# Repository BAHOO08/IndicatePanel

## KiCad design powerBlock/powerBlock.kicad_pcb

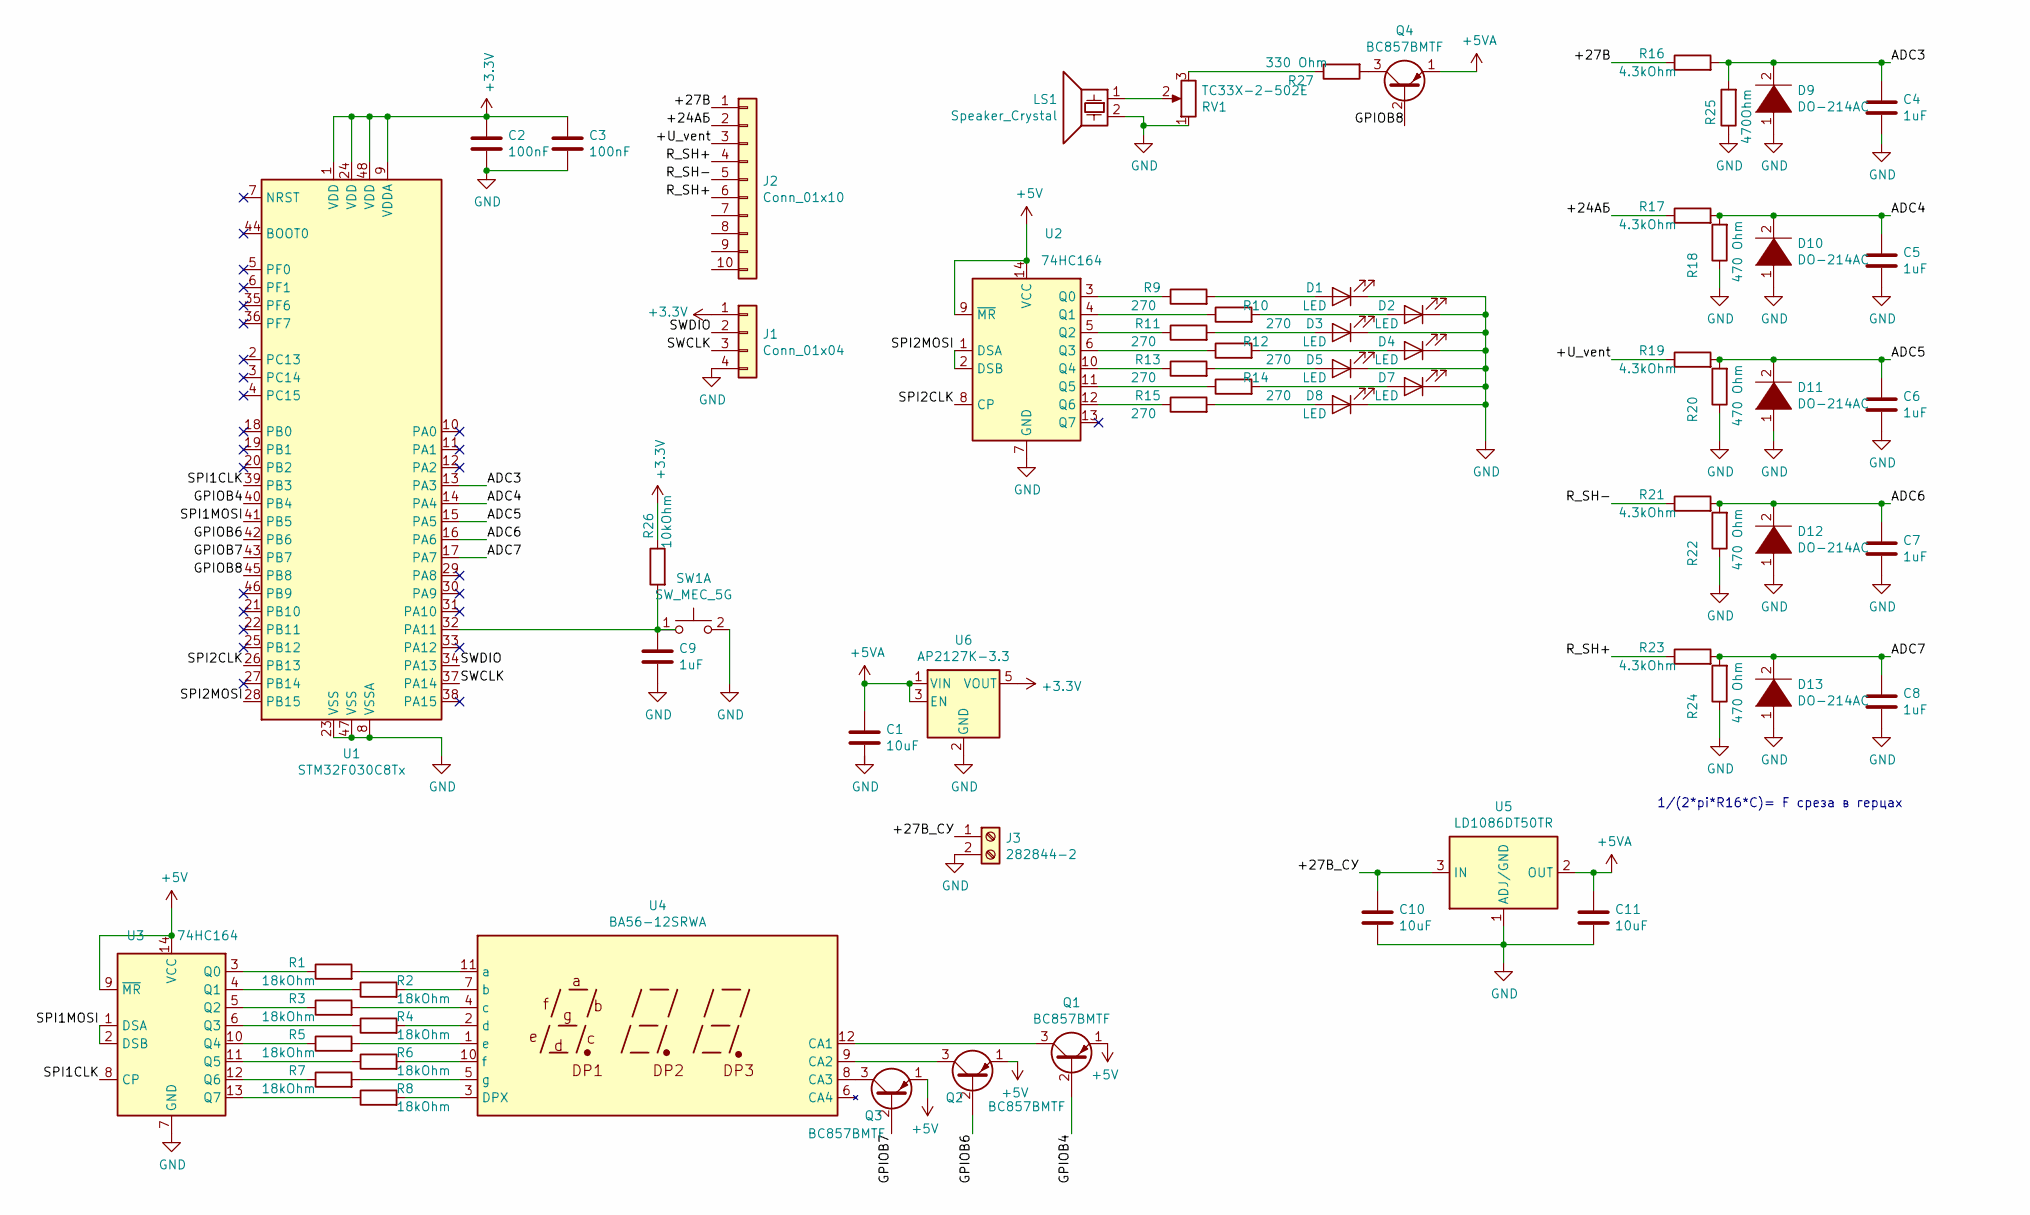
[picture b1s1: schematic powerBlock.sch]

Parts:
C1, C10, C11: 10uF; C_0603_1608Metric
C2, C3: 100nF; C_0603_1608Metric
C4, C5, C6, C7, C8, C9: 1uF; C_0603_1608Metric
D1, D2, D3, D4, D5, D7, D8: LED; LED_Rectangular_W3.9mm_H1.8mm
D9, D10, D11, D12, D13: DO-214AC; D_SMA
J1: Conn_01x04; PinHeader_1x04_P2.54mm_Vertical
J2: Conn_01x10; PinHeader_1x10_P2.54mm_Horizontal
J3: 282844-2; TerminalBlock_MetzConnect_Type175_RT02702HBLC_1x02_P7.50mm_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
LS1: Speaker_Crystal; R_LDR_10x8.5mm_P7.6mm_Vertical
Q1, Q2, Q3, Q4: BC857BMTF; SOT-23
R1, R2, R3, R4, R5, R6, R7, R8: 18kOhm; R_0603_1608Metric
R9, R10, R11, R12, R13, R14, R15: 270; R_0603_1608Metric
R16, R17, R19, R21, R23: 4.3kOhm; R_0603_1608Metric
R18, R20, R22, R24: 470 Ohm; R_0603_1608Metric
R25: 470Ohm; R_0603_1608Metric
R26: 10kOhm; R_0603_1608Metric
R27: 330 Ohm; R_0603_1608Metric
RV1: TC33X-2-502E; Potentiometer_Bourns_TC33X_Vertical
SW1: SW_MEC_5G; SW_SPST_PTS645
U1: STM32F030C8Tx; LQFP-48_7x7mm_P0.5mm
U2, U3: 74HC164; SOIC-14_3.9x8.7mm_P1.27mm
U4: BA56-12SRWA; CA56-12SEKWA
U5: LD1086DT50TR; TO-252-2
U6: AP2127K-3.3; SOT-23-5

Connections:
+3V3: C2.1, C3.1, J1.1, R26.1, U1.1 (VDD), U1.9 (VDDA), U1.24 (VDD), U1.48 (VDD), U6.5 (VOUT)
+5V: Q1.1 (E), Q2.1 (E), Q3.1 (E), U2.9 (~MR), U2.14 (VCC), U3.9 (~MR), U3.14 (VCC)
+5VA: C1.1, C11.1, Q4.1 (E), U5.2 (OUT), U6.1 (VIN), U6.3 (EN)
/+24АБ: J2.2, R17.1
/+27В: J2.1, R16.1
/+27В_СУ: C10.1, J3.1, U5.3 (IN)
/+U_vent: J2.3, R19.1
/ADC3: C4.1, D9.2 (A), R16.2, R25.2, U1.13 (PA3)
/ADC4: C5.1, D10.2 (A), R17.2, R18.2, U1.14 (PA4)
/ADC5: C6.1, D11.2 (A), R19.2, R20.2, U1.15 (PA5)
/ADC6: C7.1, D12.2 (A), R21.2, R22.2, U1.16 (PA6)
/ADC7: C8.1, D13.2 (A), R23.2, R24.2, U1.17 (PA7)
/GPIOB4: Q1.2 (B), U1.40 (PB4)
/GPIOB6: Q2.2 (B), U1.42 (PB6)
/GPIOB7: Q3.2 (B), U1.43 (PB7)
/GPIOB8: Q4.2 (B), U1.45 (PB8)
/R_SH+: J2.4, J2.6, R23.1
/R_SH-: J2.5, R21.1
/SPI1CLK: U1.39 (PB3), U3.8 (CP)
/SPI1MOSI: U1.41 (PB5), U3.1 (DSA), U3.2 (DSB)
/SPI2CLK: U1.26 (PB13), U2.8 (CP)
/SPI2MOSI: U1.28 (PB15), U2.1 (DSA), U2.2 (DSB)
/SWCLK: J1.3, U1.37 (PA14)
/SWDIO: J1.2, U1.34 (PA13)
GND: C2.2, C3.2, C4.2, C5.2, C6.2, C7.2, C8.2, C9.2, C10.2, C11.2, D1.1 (K), D2.1 (K), D3.1 (K), D4.1 (K), D5.1 (K), D7.1 (K), D8.1 (K), D9.1 (K), D10.1 (K), D11.1 (K), D12.1 (K), D13.1 (K), J1.4, J3.2, LS1.2, R18.1, R20.1, R22.1, R24.1, R25.1, RV1.1, SW1.2 (D), U1.8 (VSSA), U1.23 (VSS), U1.47 (VSS), U2.7 (GND), U3.7 (GND), U5.1 (ADJ/GND), U6.2 (GND)
unnamed: C9.1, R26.2, SW1.1 (C), U1.32 (PA11)
unnamed: D1.2 (A), R9.2
unnamed: D2.2 (A), R10.2
unnamed: D3.2 (A), R11.2
unnamed: D4.2 (A), R12.2
unnamed: D5.2 (A), R13.2
unnamed: D7.2 (A), R14.2
unnamed: D8.2 (A), R15.2
unnamed: LS1.1, RV1.2
unnamed: Q1.3 (C), U4.12 (CA1)
unnamed: Q2.3 (C), U4.9 (CA2)
unnamed: Q3.3 (C), U4.8 (CA3)
unnamed: Q4.3 (C), R27.2
unnamed: R1.1, U3.3 (Q0)
unnamed: R1.2, U4.11 (a)
unnamed: R2.1, U3.4 (Q1)
unnamed: R2.2, U4.7 (b)
unnamed: R3.1, U3.5 (Q2)
unnamed: R3.2, U4.4 (c)
unnamed: R4.1, U3.6 (Q3)
unnamed: R4.2, U4.2 (d)
unnamed: R5.1, U3.10 (Q4)
unnamed: R5.2, U4.1 (e)
unnamed: R6.1, U3.11 (Q5)
unnamed: R6.2, U4.10 (f)
unnamed: R7.1, U3.12 (Q6)
unnamed: R7.2, U4.5 (g)
unnamed: R8.1, U3.13 (Q7)
unnamed: R8.2, U4.3 (DPX)
unnamed: R9.1, U2.3 (Q0)
unnamed: R10.1, U2.4 (Q1)
unnamed: R11.1, U2.5 (Q2)
unnamed: R12.1, U2.6 (Q3)
unnamed: R13.1, U2.10 (Q4)
unnamed: R14.1, U2.11 (Q5)
unnamed: R15.1, U2.12 (Q6)
unnamed: R27.1, RV1.3

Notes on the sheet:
1/(2*pi*R16*C)= F среза в герцах

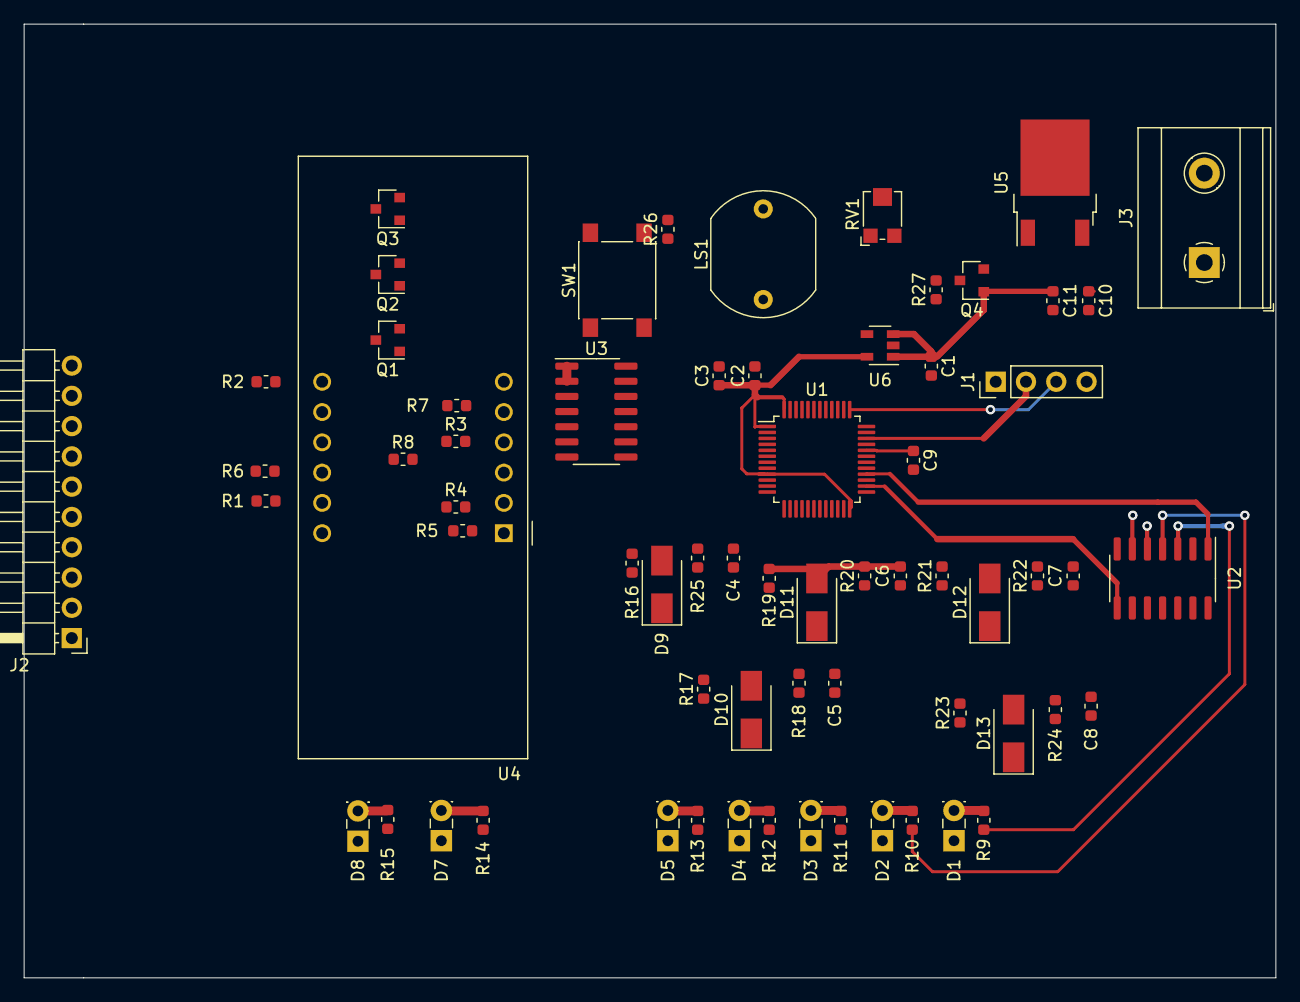
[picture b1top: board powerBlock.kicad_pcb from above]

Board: 2 copper layers, 105.0 x 80.0 mm, 66 parts (0 on the bottom side), 62 nets.

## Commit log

2020-04-08 frst cmt
2020-04-09 Добавил индикаторную панель. Подключил диод
2020-04-17 Немного допилил схему. Немного оттрассировал
